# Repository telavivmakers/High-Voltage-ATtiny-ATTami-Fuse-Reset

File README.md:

## High-Voltage-ATtiny-ATTami-Fuse-Reset

##BRANCH NOTE
this was hastliy routed using topoR router. you can find the fabbed version in the noard_topo directory. 

##notes
Based on Wayne Holder work "ATTiny Fuse Reset with 12 Volt Charge Pump" from 2010 [link](https://sites.google.com/site/wayneholder/attiny-fuse-reset-with-12-volt-charge-pump) 

With some changes:
* The collector of the Q1 transistor in Waynes diagram shorted D4 to ground via the 4 diods D1, D2, D3 and D4. Even though no harm is expected since the Arduino port pin is short circuit protected it is neater to prevent the short circuit. I moved the collector so it is connected via 1Kohm resistor.
* I changed some of the names in the schematic diagram and in the code to better depict their function.

The circuit will be build as Arduino shield with the following sockets:
* 8 pin DIP socket for 8 pin ATTiny13, ATTiny25, ATTiny45 or ATTiny85 fuse reseting/programming.
* 14 pin DIP socket for 14 pin ATTiny24, ATTiny44 or ATTiny84 fuse reseting/programming.
* Headers and POGO-PIN fixture for reseting/programming [ATTami](https://github.com/telavivmakers/at-tami) boards.

###todo
* TARGET/ ISP VCC switch must die
*

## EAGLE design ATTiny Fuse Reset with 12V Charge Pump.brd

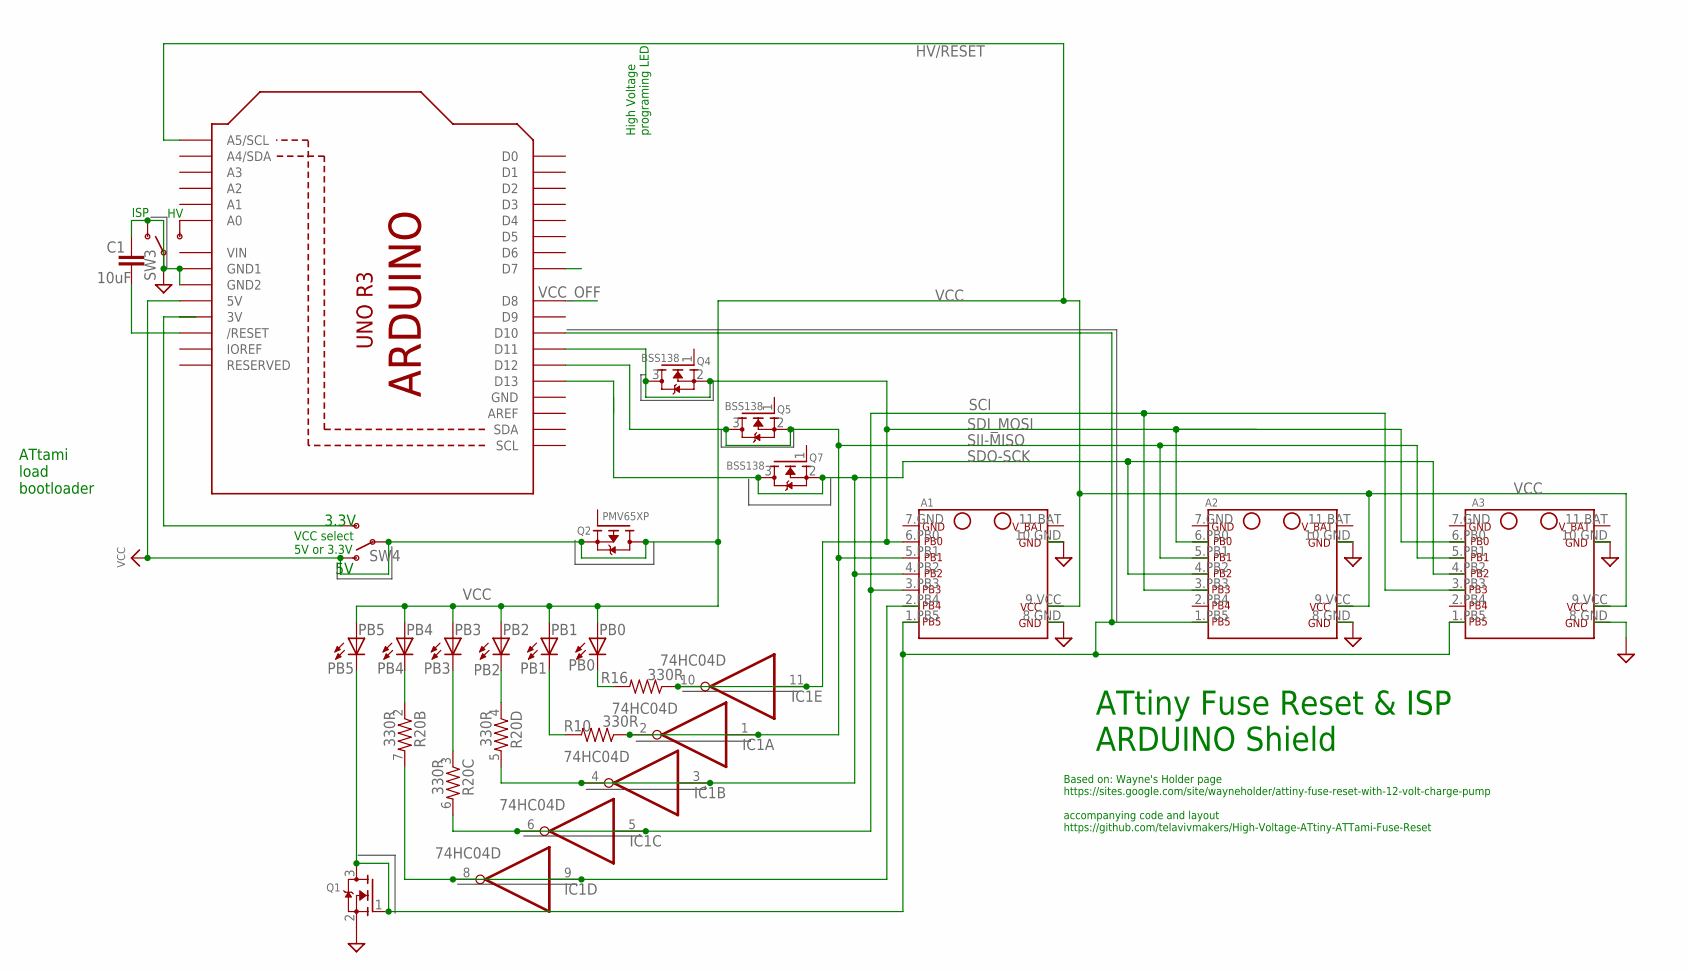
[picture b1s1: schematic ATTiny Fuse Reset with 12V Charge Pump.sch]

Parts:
A1: ATTami; BREAKOUT_TAMI_NOHOLES
A2: ATTANI_BREAKOUT_PINSHOLES; BREAKOUT_ATTAMI
A3: ATTANI_BREAKOUT_PINSNOHOLE; BREAKOUT_TAMI_NOHOLES
C1: 10uF; 0805
IC1: 74HC04D; SO14
PB0: PB0; LED-805
PB1: PB1; LED-805
PB2: PB2; LED-805
PB3: PB3; LED-805
PB4: PB4; LED-805
PB5: PB5; LED-805
Q1: MOSFET-NREFLOW; SOT23-R
Q2: PMV65XP; SOT23-R
Q4, Q5, Q7: BSS138; SOT23-R
R10, R16: 330R; 0805
R20: 330R; 0603-ARV
SW3, SW4: SWITCH_SPDT; KPS-1290
U1: ARDUINOR3-BPLACE

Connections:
GND: A1.8.GND (GND), A1.10.GND (GND), A2.8.GND (GND), A2.10.GND (GND), A3.8.GND (GND), A3.10.GND (GND), C1.1, IC1.7 (GND), Q1.2 (S), SW3.O, SW3.P, U1.GND, U1.GND1, U1.GND2
HV/RESET: A1.1.PB5 (PB5), A2.1.PB5 (PB5), A3.1.PB5 (PB5), PB5.C, Q1.1 (G), Q1.3 (D), U1.D10
unnamed: SW3.S, U1.A0
unnamed: SW4.S, U1.3V
unnamed: PB2.C, R20.4 (1)
unnamed: PB1.C, R10.2
unnamed: PB0.C, R16.2
unnamed: A1.2.PB4 (PB4), IC1.8 (O), IC1.9 (I), R20.7 (2)
unnamed: PB3.C, R20.3 (1)
unnamed: PB4.C, R20.2 (1)
unnamed: C1.2, U1.RESET (/RESET)
SCI: A2.3.PB3 (PB3), A3.3.PB3 (PB3), IC1.5 (I), IC1.6 (O), R20.6 (2)
SDI_MOSI: A2.6.PB0 (PB0), A3.6.PB0 (PB0), IC1.10 (O), IC1.11 (I), Q4.2 (S), Q4.3 (D), R16.1, U1.D11
SDO-SCK: A2.4.PB2 (PB2), A3.4.PB2 (PB2), IC1.3 (I), IC1.4 (O), Q7.2 (S), Q7.3 (D), R20.5 (2), U1.D13
SII-MISO: A2.5.PB1 (PB1), A3.5.PB1 (PB1), IC1.1 (I), IC1.2 (O), Q5.2 (S), Q5.3 (D), R10.1, U1.D12
VCC: A1.9.VCC (VCC), A2.9.VCC (VCC), A3.9.VCC (VCC), IC1.14 (VCC), PB0.A, PB1.A, PB2.A, PB3.A, PB4.A, PB5.A, Q2.2 (S), Q2.3 (D), SW4.O, SW4.P, U1.5V, U1.A5 (A5/SCL)
VCC_OFF: U1.D8
VIN: U1.VIN

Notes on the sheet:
ATtiny Fuse Reset & ISP ARDUINO Shield
Based on: Wayne's Holder page https://sites.google.com/site/wayneholder/attiny-fuse-reset-with-12-volt-charge-pump accompanying code and layout https://github.com/telavivmakers/High-Voltage-ATtiny-ATTami-Fuse-Reset
ISP
High Voltage programing LED
3.3V
ATtami load bootloader
VCC select 5V or 3.3V

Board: 2 copper layers, 22 parts (1 on the bottom side), 16 nets, no tracks yet.

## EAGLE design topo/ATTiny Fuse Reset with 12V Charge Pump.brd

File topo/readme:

this was generated using the (freeware) topoR lite.

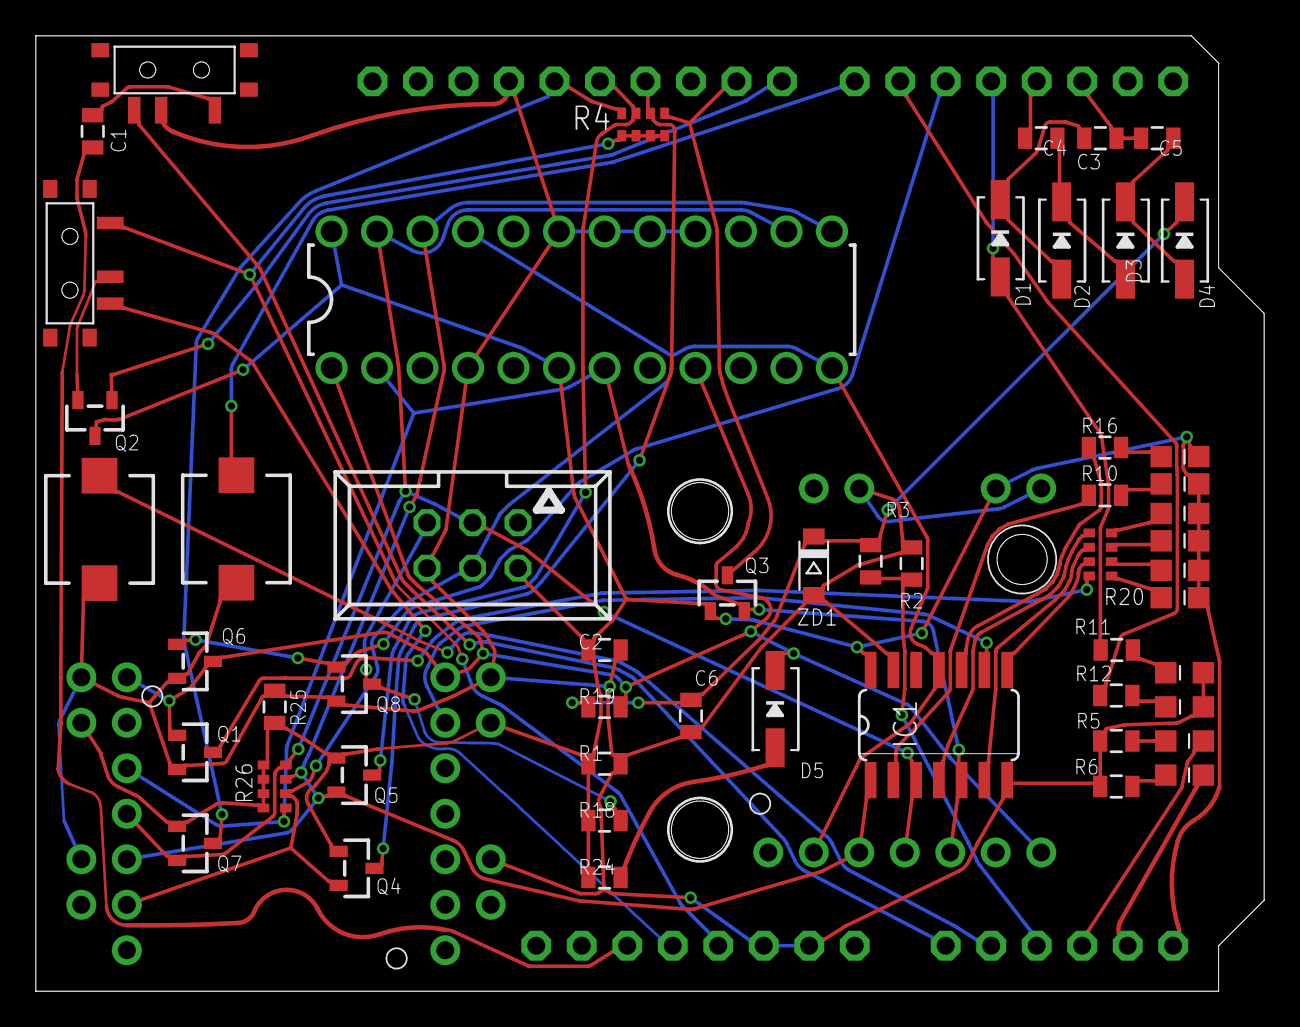
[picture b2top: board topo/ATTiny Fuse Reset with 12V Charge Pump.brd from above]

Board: 2 copper layers, 68.6 x 53.3 mm, 57 parts (1 on the bottom side), 51 nets.

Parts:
A1, A3: BREAKOUT_TAMI_NOHOLES
A2: BREAKOUT_ATTAMI
C1, C2, C3, C4, C5, C6: 0805
D1, D2, D3, D5: SOD-323
D4: 1N4148; SOD-323
HBEAT: H.B.; LED-805
HV_O: HV; LED-805
IC1: SO14
ISP: PMD; LED-805
ISP_ERR: ERR; LED-805
PB0: PB0; LED-805
PB1: PB1; LED-805
PB2: PB2; LED-805
PB3: PB3; LED-805
PB4: PB4; LED-805
PB5: PB5; LED-805
Q1, Q2, Q3, Q4, Q5, Q6, Q7, Q8: SOT23-R
R1, R2, R3, R5, R6, R10, R11, R12, R16, R18, R19, R24, R25: 0805
R4, R20, R26: 0603-ARV
SW1, SW2: PUSHBUTTON_SMD_SJ
SW3: KPS-1290
SW4: SWITCH_SPDT; KPS-1290
U1: ARDUINOR3-BPLACE
U$2: DIL-24-ZIF
X1: 057-006-1
ZD1: SOD-123

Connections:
11.5V: C6.1, D4.CQ, R3.2, R19.2, ZD1.C
ATTINY_VCC: A1.9.VCC, A2.9.VCC, A3.9.VCC, C2.1, IC1.14, PB0.A, PB1.A, PB2.A, PB3.A, PB4.A, PB5.A, Q2.3, Q3.1, Q4.1, Q5.1, Q7.1, R1.1, R18.2, R24.1, R25.1, R26.5, R26.6, R26.7, R26.8, U1.A5, U$2.P$6, U$2.P$24, X1.2
GND: A1.8.GND, A1.10.GND, A2.8.GND, A2.10.GND, A3.8.GND, A3.10.GND, C2.2, C6.2, HBEAT.C, HV_O.C, IC1.7, IC1.13, Q1.2, Q6.2, Q8.2, R1.2, R2.1, R5.2, R6.2, R25.2, SW1.P$1, SW2.P$1, SW3.P, U1.GND, U1.GND1, U1.GND2, U$2.P$4, U$2.P$16, U$2.P$17, U$2.P$18, U$2.P$19, X1.6, ZD1.A
HV/RESET: A1.1.PB5, A2.1.PB5, A3.1.PB5, D5.CQ, Q1.1, Q6.3, R19.1, U$2.P$1, U$2.P$9
HV_OFF(RESET): Q6.1, Q8.1, U1.D5
HV_SENSE: R2.2, R3.1, U1.A2
ISP_RESET: Q8.3, R18.1, X1.5
unnamed: Q2.2, SW4.P
unnamed: Q3.3, R4.1, U1.D9
unnamed: SW3.S, U1.A0
unnamed: HV_O.A, R11.1
unnamed: D5.AQ, R24.2
unnamed: ISP.C, R5.1
unnamed: A1.2.PB4, IC1.9
unnamed: Q4.3, R4.2, U1.D11
unnamed: SW1.P$2, U1.A1
unnamed: C3.1, D1.CQ, D2.AQ
unnamed: C4.1, D2.CQ, D3.AQ
unnamed: C5.1, D3.CQ, D4.AQ
unnamed: IC1.10, R16.1
unnamed: C1.1, SW3.O
unnamed: ISP_ERR.C, R6.1
unnamed: SW4.S, U1.3V
unnamed: ISP_ERR.A, U1.A4
unnamed: ISP.A, U1.A3
unnamed: R12.1, U1.D6
unnamed: HBEAT.A, R12.2
unnamed: IC1.2, R10.1
unnamed: SW2.P$2, U1.D7
unnamed: PB2.C, R20.4
unnamed: IC1.4, R20.5
unnamed: PB1.C, R10.2
unnamed: IC1.6, R20.6
unnamed: PB0.C, R16.2
unnamed: IC1.8, R20.7
unnamed: PB3.C, R20.3
unnamed: PB4.C, R20.2
unnamed: PB5.C, R20.1
unnamed: Q1.3, R20.8
unnamed: C1.2, U1.RESET
unnamed: Q7.3, R4.4, U1.D13
unnamed: Q5.3, R4.3, U1.D12
P1: C3.2, C5.2, U1.D2
P2: C4.2, U1.D3
PUMP_VCC: D1.AQ, R11.2, U1.D4
SCI: A2.3.PB3, A3.3.PB3, IC1.5, Q3.2, R26.1, U$2.P$2, U$2.P$7
SDI_MOSI: A2.6.PB0, A3.6.PB0, IC1.11, Q4.2, R26.2, U$2.P$12, U$2.P$21, X1.4
SDO-SCK: A2.4.PB2, A3.4.PB2, IC1.3, Q7.2, R26.4, U$2.P$14, U$2.P$23, X1.3
SII-MISO: A2.5.PB1, A3.5.PB1, IC1.1, Q5.2, R26.3, U$2.P$13, U$2.P$22
VCC: R4.5, R4.6, R4.7, R4.8, SW4.O, U1.5V
VCC_OFF: Q2.1, U1.D8

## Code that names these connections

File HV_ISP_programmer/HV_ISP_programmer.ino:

#include <TimerOne.h>

#define ATtiny_VCC      8		//target VCC
#define LED_HB		6		//Yellow LED, was 9 in the original design. As for now I'm not using the LEDs in the shield
#define HV_ISP_select   A0	        //HV ISP toggle switch
#define ATTami_test     A1		//check if ATTami test push button is pressed.
#define ATTami_bootloader A2            //check if ATTami load bootloader push button is pressed.
#define HV_sense	A3		// Analog read of a sample of the 11.5V produced by the charge pump circuit
#define LED_PMODE	A4		//Green LED, was 7 in the original design.
#define LED_ERR		A5		//Red LED, was 8 in the original design.
#define RESET		5		// pin 5 is also reffered to as HV_off in "ATTinyFuseReset" file
#define SCI		9		// D9, Target Clock
#define SDO		13		// D13, Target Data Output
#define SII		12		// D12, Target Instruction Input
#define SDI		11		// D11,  Target Data Input

byte switches_old; //keeps the old position of HV_ISP_select, ATTami_test and ATTami_bootloader switches
byte switches_new; //keeps the new position of HV_ISP_select, ATTami_test and ATTami_bootloader switches

void setup() {
  Serial.begin(19200);
  pinMode(10, OUTPUT); // Ensures that the built in ATMEGA328 SPI SS would not read the pin as LOW
  digitalWrite(10, HIGH);
  pinMode(ATtiny_VCC, OUTPUT);
  //The following 3 LEDs are used in ISP mode only
  pinMode(LED_HB, OUTPUT);
  pinMode(LED_PMODE, OUTPUT);
  pinMode(LED_ERR, OUTPUT);
  Timer1.initialize(500);
  Timer1.attachInterrupt(ticker);
  //The following pins are used by the HV programmer in "ATTinyFuseReset" file.
  pinMode (A1, OUTPUT); // used to toggle A1 output pin on every pass through the loop in the ISR (or ticker) routine on "ATTinyFuseReset" file. It should be removed in the final version.
  pinMode(SDI, OUTPUT);
  pinMode(SII, OUTPUT);
  pinMode(SCI, OUTPUT);
  pinMode(SDO, OUTPUT);     // Will be configured as INPUT when in "ArduinoISP_ATTami" file
  analogReference(DEFAULT);
  pinMode (RESET, OUTPUT);
  digitalWrite(HV_ISP_select, HIGH); //activates the "HV_ISP_select" pin pullUp resistor.
  digitalWrite(ATTami_test, HIGH); //activates the "ATTami_test" pin pullUp resistor.
  digitalWrite(ATTami_bootloader, HIGH); //activates the "ATTami_bootloader" pin pullUp resistor.
}

void loop(){
  for (int i=0; i<=50; i++){
    switches_new = PINC & B00000111;
    if (switches_new != switches_old) i=0;
    switches_old = switches_new;
    delay (1);
  }
  if ((switches_new & B00000110) == B00000110){ // no push button is pressed
    if (switches_new & B00000001) { // ISP mode
      TIMSK1 &= ~1<<TOIE1; //disable 12V pump, see: ticker() function in "ATTinyFuseReset" file
      pinMode(LED_HB, OUTPUT);
      pinMode(LED_PMODE, OUTPUT);
      pinMode(LED_ERR, OUTPUT);
      pulse(LED_HB, 2);
      pulse(LED_PMODE, 2);
      pulse(LED_ERR, 2);
      Serial.println("\nGoing into ISP mode");
      Serial.println("Under Tools/Board menu choose the appropriate ATTiny device");
      Serial.println("Under Tools/Programmer menu choose Arduino as ISP");
      Serial.println("and Upload your sketch");
      ISPloop();
    }
    else { // HV mode
      TIMSK1 |= 1<<TOIE1; //enable 12V pump, see: ticker() function in "ATTinyFuseReset" file
      digitalWrite (ATtiny_VCC, LOW);
      digitalWrite(LED_HB, HIGH);
      HVloop();
    }
  }
  else{ // one of the push buttons is pressed
    TIMSK1 &= ~1<<TOIE1; //disable 12V pump, see: ticker() function in "ATTinyFuseReset" file
    if (switches_new & B00000010){    //ATTAmi test
      Serial.println("\nGoing into ATTiny test mode");
      ATTami_test_mode(); 
    }
    else if (switches_new & B00000100){ //ATTAmi load bootloader
      Serial.println("ATTami load bootloader");
      ATTami_load_bootloader();
    }
  }
} 

void ATTami_test_mode(){
  TIMSK1 &= ~1<<TOIE1; //disable 12V pump, see: ticker() function in "ATTinyFuseReset" file
  digitalWrite (LED_HB, LOW);
  digitalWrite(ATtiny_VCC, HIGH);
  digitalWrite(RESET, LOW);
  while (switches_new == (PINC & B00000111));
  digitalWrite(ATtiny_VCC, LOW);
  digitalWrite(RESET, HIGH);
}

void ATTami_load_bootloader(){
  Serial.println("Yet not implemented.");
}

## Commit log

2015-01-13 schematic base version
2015-01-13 sketch base version
2015-01-14 version with dip8 and dip14
2015-01-14 need to add ISP header
2015-01-15 added 1N4148 value
2015-01-16 some caretaking
2015-01-16 reference calibrated to achieve High Voltage of 11.5 volts
2015-01-17 added ignore file
2015-01-17 ignored
2015-01-17 replaced by ATTinyFuseReset3.ino
2015-01-17 More detailed information sent to the terminal.
    The program is basically the same as ATTinyFuseReset3.ino. I improved
    the dialog with the user to be more clear.
2015-01-17 More accurate description of the project.
    Added list of programmed MCUs
2015-01-17 error correction
2015-01-17 print formatting
2015-01-18 started library of parts
2015-01-18 Added 12V protecting Zener
2015-01-18 Some cosmetic changes
2015-01-19 layout and package of attami added
2015-01-19 Mirroring one of the ATTami packages
2015-01-19 Changes in the schematic
    MOSI, MISO, SCK and 12V_OFF are now connected to the correct pins of the
    Arduino UNO
2015-01-19 error correction: ATTINY_VCC wire was not connected
2015-01-19 Some more corrections
2015-01-19 Updating the sketch
    Updating the sketch to comply with the updated schematic
    For the time being the sketch only deal with ATTiny fuses reset.
    Next step will be adding ISP capability.
2015-01-20 R6, R10 and R11 values changed
2015-01-20 Sketch to run ISP part as stand alone
2015-01-20 combining HV reset with ISP slave select
2015-01-21 Revert "combining HV reset with ISP slave select"
    This reverts commit 8866a214dde31db0049427def42afcfb88113351.
2015-01-22 The sketch updated to support latest board design
2015-01-24 Changes in the schematic
2015-01-24 changed attiny breakout size
2015-01-24 ATTami components connected
2015-01-25 Added 3 LEDs. The LEDs indicate activity and error
2015-01-26 merged devices into one lib
2015-01-26 removed values, kept names
    need to move throuhole compenents from above the usb connector
2015-01-26 added .job to ignore
2015-02-10 Added features
    1. Ability to program 5V or 3.3V devices.
    2. ATTami acceptance test.
    3. Uploading of ATTami bootloader directly from ARDUINO memory.
2015-02-10 Sketches to support the new hardware design
    The 3 sketches HV_ISP_programmer.ino, ATTinyFuseReset.ino and
    ArduinoISP_ATTami.ino have to be under HV_ISP_programmer directory.
    Use Arduino IDE to open and upload HV_ISP_programmer.ino
2015-02-11 Isolate the +12V from the ISP sockets
    3 N channel MOS-FET transistors are used in order to isolate the +12V
    from components which are not supposed to get high voltage
2015-02-11 added prefix and ran renumber ULP, also cosmetics on schema
2015-02-11 update PDF
2015-02-12 Reshuffle Arduino I/O pins. New look for the "ATTAMI_BREAKOUT_SHEILD"
    At this stage the software is not consistent with the new Arduino pin
    arrangement. It will be fixed soon.
2015-02-12 Software updated to reflect changes in the hardware design
2015-02-13 Added four N channel MOS-FET bidirectional 3.3 to 5 V level shifters
2015-02-14 Same diagram, better arranged.
2015-02-18 Added features and improved user interface
2015-02-21 Improved menu
2015-02-22 Parts renumber and partial placement attempt
2015-02-24 Schematic and board layout improvment
2015-02-24 HV ISP programmer presentation in multiple formats
2015-02-27 deleting duplicate file with different format
2015-02-27 "TARGET/ ISP VCC switch"-B-Gone
2015-03-02 added array resistors, moved transistor under attami
2015-03-02 zif inside, aded to lib, removed 10 pin ISP
2015-03-02 added clean arduino board, replaced attami with new parts from the lib
2015-03-02 zif24
2015-03-02 zif24 ito brd
2015-03-02 some more
2015-03-03 whaa
2015-03-09 removed pins from silkscreen on arduino device
2015-03-10 Captions added
2015-03-16 added .rpo and .job to ignore file
2015-03-16 bit order and removed unsued layers
2015-03-16 working on routng
2015-03-17 more routing, now switching for topoR
2015-03-17 added dimnsion layer
2015-03-17 aligned xtra pins overlayed on attami device
2015-03-18 topoR first effort, not bad
2015-03-26 branch to fix issues with borked master
2015-03-26 issues fixed
    the two pins are connected now.
    the Vin issue is ignored (actually this pin is an output of the Arduino)
2015-03-28 ordered name layer with silkscreen. to silkscreen use tNames,tPlaces, tDocu, Names layers
2015-03-28 added pdf
2015-04-02 Some captions changed
2015-04-07 lib chnages
2015-08-04 added 4layer version, WIP
2015-08-05 new brd with 4layer
2015-08-05 new brd with 4layer, tnames fix
2015-08-06 fixied traces in 4layer board, version in board-topor go to fab
2015-08-08 sent to fab
2016-09-22 fab caniudate from topoR
2016-09-23 more topoR
2016-10-04 changed board layout
2016-10-05 gebrrized
2016-10-06 ignore'
2016-10-06 got corrct brd/sch from fixing_issue branch
2016-10-06 cleanning
2016-10-07 adde pdf
2016-11-14 readme update
2016-11-14 removed componenets not used, added jumpers
2016-11-14 added more jumpers, PB5
2016-11-14 add board pdf
2016-11-14 q4 jumper pinked

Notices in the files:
parts and their libraries:
microbuilder: This work is placed in the public domain, and may be freely used for commercial and non-commercial work with the following conditions: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
SparkFun-Electromechanical: Licensing: CC v3.0 Share-Alike You are welcome to use this library for commercial purposes.
